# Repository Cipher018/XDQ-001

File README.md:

# XDQ-001

## Introduction

## What is XDQ-001?

The **XDQ-001**, or **Experimental Drone Quadcopter Model 001**, is a flight platform with an original design. Its experimental objective is to achieve a FPV quadcopter capable of both acrobatic flight and cinematic filming. Furthermore, the XDQ-001 platform serves as a cutting-edge testbed for implementing highly optimized low-level control and autonomous navigation algorithms.

## Whats New?

The **XDQ-001** represents a massive generational leap over its predecessor (XDF-001), integrating the following hardware and firmware innovations (Version V001):

1. **Hybrid Cooperative Interrupt-Based Architecture (No RTOS):**
   - **1000Hz Critical Loop:** Hardware Timer ISR dedicated exclusively to attitude (AHRS), PID calculations, and motor control.
   - **50Hz Kinematic Loop:** Background loop for Kalman filtering, waypoint navigation, and geometric estimation.
2. **Dual-Layer Navigation System:**
   - **Layer 1 (Attitude):** Optimized Mahony AHRS filter running at 1000Hz.
   - **Layer 2 (Kinematics):** Three-Dimensional Error State Kalman Filter (3D ESKF) at 50Hz, fusing accelerometer, GPS, and barometer (BMP280) measurements.
3. **CADI_A Adaptive Navigation System:**
   - Advanced algorithms for L1 navigation (adaptive waypoints) and Orbit (loiter).
   - **Stochastic Wind Estimator (Pitot-less):** Calculates and compensates for crosswind in real-time without requiring a pitot tube, based on geometric discrepancy during turns.
4. **Advanced Flight Control (FlightPID):** Isolated bandwidth PIDs (LPF_PT1 filters on P and D terms).
5. **Dynamic Safety Guards:**
   - *Dynamic Stall Guard:* Dynamic stall prevention based on bank angle.
   - *G-Limiter:* Pilot control limitation when the safe structural G-load (2.0G - 3.5G) is exceeded.
   - *Failsafe RTL:* Safe automatic Return-To-Launch on link loss.
6. **Dedicated Hardware:** MCU STM32F4 (with FPU), dedicated ICM-42688 IMU, MMC5983MA external magnetometer, and SX1280 long-range modem.
7. **Secure Communications & Telemetry:** Frequency Hopping Spread Spectrum (FHSS), logical dual-pipe, and strong cross-block encryption (XXTEA) with integrated CRC16.
8. **Uninterrupted Blackbox Logging:** Lock-free Ping-Pong buffers linked via DMA to the W25Q32JVSS Flash memory.

## Objectives

The primary objective is to develop an exceptional FPV quadcopter capable of both extreme acrobatic flight and smooth cinematic tracking.

The secondary objectives are:
- Provide an ultra-fast, predictable, non-RTOS software framework.
- Consolidate the capabilities of the CADI autonomous ecosystem (Waypoints, Orbits, auto RTL).
- Implement and refine stochastic estimation systems (ESKF and Wind Estimator).
- Establish an impenetrable telemetry system (robust encryption and FHSS).

## Architecture

As previously mentioned, the project is based on the STM32F4 architecture utilizing a hybrid cooperative interrupt-based system. You can consult the documentation section for details regarding the PCB, algorithms, or flowcharts.

## Hardware

The XDQ-001 uses a custom Flight Control Board (FCB) built around the **STM32F4** microcontroller. Key sensors and components:

- **IMU (Gyro/Accel):** ICM‑42688‑P
- **Magnetometer:** MMC5983MA
- **Barometer:** BMP280
- **Radio Link:** SX‑1280 (FHSS Support)
- **Storage:** W25Q32JVSS Flash Memory
- **Camera:** Caddx Baby Ratel 2 (optional)

A full Bill of Materials (BOM) is still being defined.

## Software

- Development is currently performed using the **Arduino IDE** (with the STM32 core) but migration to a more advanced toolchain is planned.
- No ground control station (GCS) software exists yet; a future GCS will communicate via the SX‑1280 radio.

## Compilation & Installation

The firmware follows the standard Arduino IDE project layout:

1. Open the `Firmware/` folder and load `XDQ-001F_V001.ino`.
2. Select the appropriate **STM32F4** board definition.
3. Ensure FPU support is enabled if required.
4. Verify / compile the sketch (`Ctrl+R`) and upload using a compatible programmer (e.g., ST-Link V2) or USB DFU bootloader.

## Usage

1. Power the FCB and connect the radio module.
2. Power the drone and perform a basic motor test (ensure propellers are removed).
3. When the GCS becomes available, pair it with the SX‑1280 radio and start telemetry.

## Configuration

At present the firmware has no runtime‑configurable parameters. Future releases will expose PID and filter tuning via the GCS.

## Contributing

Contributions are welcome under an **MIT license**. Please:

- Fork the repository and create a feature branch.
- Follow the existing code style (Arduino‑C++ with descriptive comments).
- Ensure any additions maintain the non-blocking philosophy of the 1000Hz critical loop.
- Open a Pull Request with a clear description of changes.

## License

This project is licensed under the **MIT License**. See the `LICENSE` file for details.

## Documentation

It is highly recommended to review the comprehensive documentation to understand the mathematical and algorithmic details:

- 📄 **[Firmware Reference Manual (Markdown)](Documentation/firmware_reference.md)**
- 📕 **[Firmware Reference Manual (PDF)](Documentation/firmware_reference.pdf)**
- 📐 [Architecture Diagram](Documentation/architecture.md) (Pending migration)
- 🔌 [Pinout & Hardware](Documentation/pinout.md) (Pending migration)
- 📡 [Protocols](Documentation/protocol.md) (Pending migration)

## Project Structure

The repository is organized as follows:

- **Firmware/** – Arduino sketch source files (`*.ino`, drivers, control algorithms, telemetry).
- **Documentation/** – Design documents, architecture diagrams, pin‑out tables, protocol specifications, and other reference material.
- **CAD/** – 3D models and mechanical drawings for printable parts.
- **PCB/** – PCB design files, gerbers, and component placement.
- **References/** – Datasheets, application notes, and external resources used during development.
- **README.md** – This high‑level overview.
- **LICENSE** – MIT license file.

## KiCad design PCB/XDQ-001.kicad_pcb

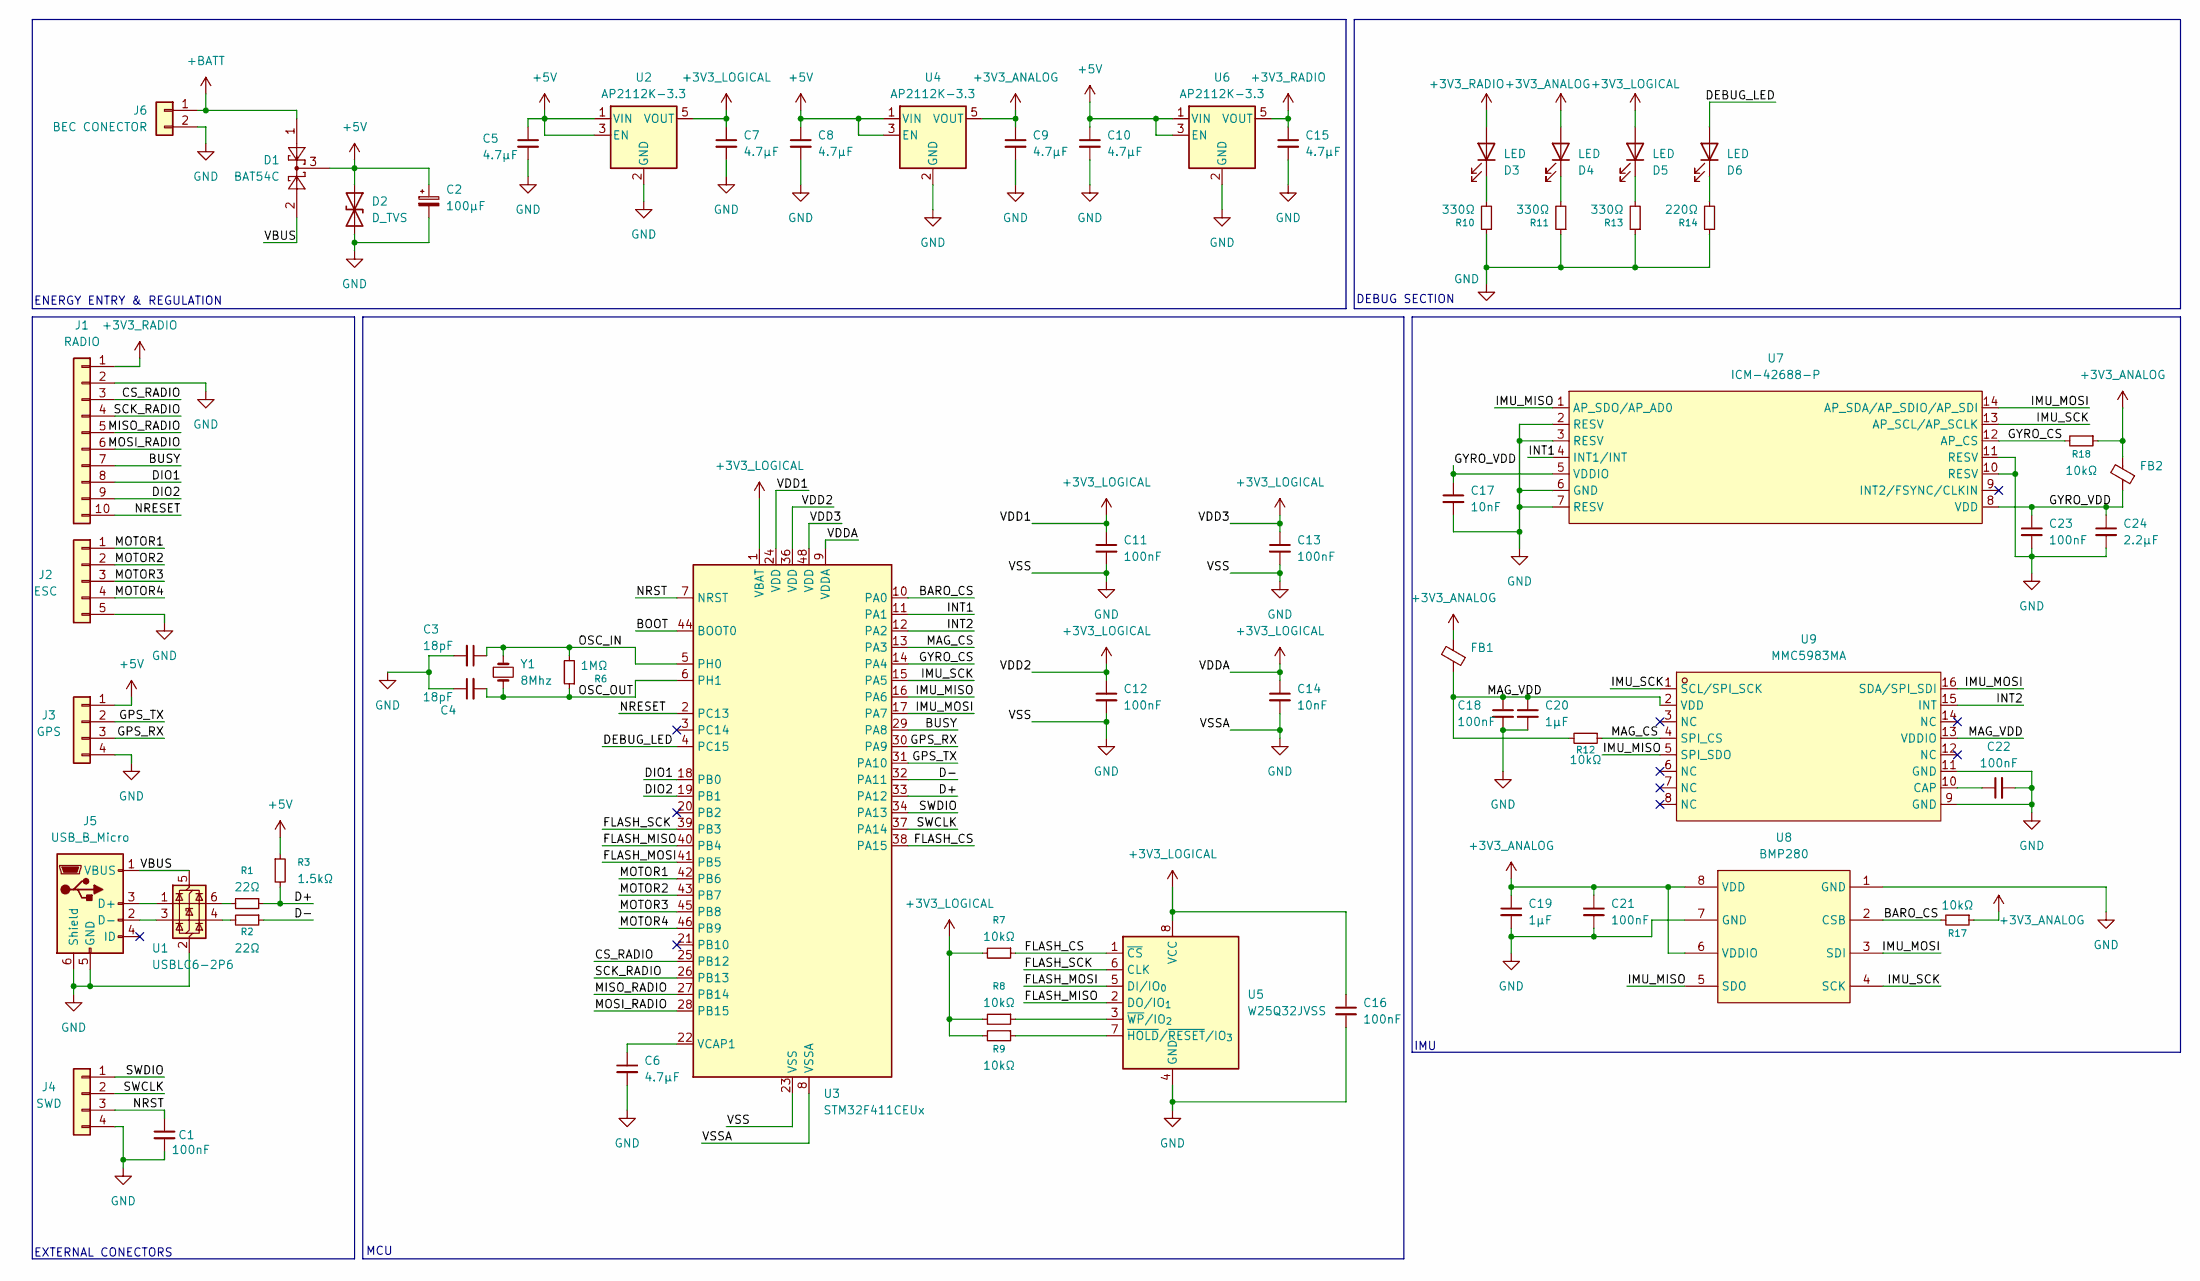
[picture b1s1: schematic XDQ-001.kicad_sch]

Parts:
C1, C11, C12, C13, C16, C18, C21, C22, C23: 100nF; C_0402_1005Metric_Pad0.74x0.62mm_HandSolder
C2: 100µF; CP_Elec_5x5.3
C3, C4: 18pF; C_0402_1005Metric_Pad0.74x0.62mm_HandSolder
C5, C6, C7, C8, C9, C10, C15: 4.7µF; C_0603_1608Metric_Pad1.08x0.95mm_HandSolder
C14, C17: 10nF; C_0402_1005Metric_Pad0.74x0.62mm_HandSolder
C19, C20: 1µF; C_0603_1608Metric_Pad1.08x0.95mm_HandSolder
C24: 2.2µF; C_0402_1005Metric_Pad0.74x0.62mm_HandSolder
D1: BAT54C; SOT-23
D2: D_TVS; D_SMB
D3, D4, D5, D6: LED; LED_0603_1608Metric_Pad1.05x0.95mm_HandSolder
FB1, FB2: FerriteBead_Small; L_0402_1005Metric
J1: RADIO; SolderWirePad_1x10_SMD_1.5x3mm
J2: ESC; SolderWirePad_1x05_SMD_1.5x3mm
J3: GPS; JST_PH_B4B-PH-K_1x04_P2.00mm_Vertical
J4: SWD; JST_PH_B4B-PH-K_1x04_P2.00mm_Vertical
J5: USB_B_Micro; USB_Micro-B_GCT_USB3076-30-A
J6: BEC CONECTOR; JST_PH_B2B-PH-K_1x02_P2.00mm_Vertical
R1, R2: 22Ω; R_0402_1005Metric_Pad0.72x0.64mm_HandSolder
R3: 1.5kΩ; R_0402_1005Metric_Pad0.72x0.64mm_HandSolder
R6: 1MΩ; R_0402_1005Metric_Pad0.72x0.64mm_HandSolder
R7, R8, R9, R12, R17, R18: 10kΩ; R_0402_1005Metric_Pad0.72x0.64mm_HandSolder
R10, R11, R13: 330Ω; R_0402_1005Metric_Pad0.72x0.64mm_HandSolder
R14: 220Ω; R_0402_1005Metric_Pad0.72x0.64mm_HandSolder
U1: USBLC6-2P6; SOT-666
U2, U4, U6: AP2112K-3.3; SOT-23-5
U3: STM32F411CEUx; QFN-48-1EP_7x7mm_P0.5mm_EP5.6x5.6mm
U5: W25Q32JVSS; SOIC-8_5.3x5.3mm_P1.27mm
U7: ICM-42688-P; LGA-14_L3.0-W2.5-P0.50-TL; MPN ICM-42688-P; LCSC Part C1850418
U8: BMP280; LGA-8_L2.5-W2.0-P0.65_AMP6127; MPN BMP280; LCSC Part C83291
U9: MMC5983MA; LGA-16_L3.0-W3.0-P0.50-BL_SQ; MPN MMC5983MA; LCSC Part C404329
Y1: 8Mhz; Crystal_SMD_2012-2Pin_2.0x1.2mm_HandSoldering

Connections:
+3V3_ANALOG: C9.1, C19.1, C21.1, D4.2 (A), FB1.2, FB2.2, R17.1, R18.1, U4.5 (VOUT), U8.6 (VDDIO), U8.8 (VDD)
+3V3_LOGICAL: C7.1, C11.1, C12.1, C13.1, C14.1, C16.1, D5.2 (A), R7.2, R8.2, R9.2, U2.5 (VOUT), U3.1 (VBAT), U3.9 (VDDA), U3.24 (VDD), U3.36 (VDD), U3.48 (VDD), U5.8 (VCC)
+3V3_RADIO: C15.1, D3.2 (A), J1.1, U6.5 (VOUT)
+5V: C2.1, C5.1, C8.1, C10.1, D1.3, D2.1 (A1), J3.1, R3.1, U2.1 (VIN), U2.3 (EN), U4.1 (VIN), U4.3 (EN), U6.1 (VIN), U6.3 (EN)
+BATT: D1.1, J6.1
/BARO_CS: R17.2, U3.10 (PA0), U8.2 (CSB)
/BOOT: U3.44 (BOOT0)
/BUSY: J1.7, U3.29 (PA8)
/CS_RADIO: J1.3, U3.25 (PB12)
/D+: R1.1, R3.2, U3.33 (PA12)
/D-: R2.1, U3.32 (PA11)
/DEBUG_LED: D6.2 (A), U3.4 (PC15)
/DIO1: J1.8, U3.18 (PB0)
/DIO2: J1.9, U3.19 (PB1)
/FLASH_CS: R7.1, U3.38 (PA15), U5.1 (~CS)
/FLASH_MISO: U3.40 (PB4), U5.2 (DO/IO_{1})
/FLASH_MOSI: U3.41 (PB5), U5.5 (DI/IO_{0})
/FLASH_SCK: U3.39 (PB3), U5.6 (CLK)
/GPS_RX: J3.3, U3.30 (PA9)
/GPS_TX: J3.2, U3.31 (PA10)
/GYRO_CS: R18.2, U3.14 (PA4), U7.12 (AP_CS)
/GYRO_VDD: C17.1, C23.1, C24.1, FB2.1, U7.5 (VDDIO), U7.8 (VDD)
/IMU_MISO: U3.16 (PA6), U7.1 (AP_SDO/AP_AD0), U8.5 (SDO), U9.5 (SPI_SDO)
/IMU_MOSI: U3.17 (PA7), U7.14 (AP_SDA/AP_SDIO/AP_SDI), U8.3 (SDI), U9.16 (SDA/SPI_SDI)
/IMU_SCK: U3.15 (PA5), U7.13 (AP_SCL/AP_SCLK), U8.4 (SCK), U9.1 (SCL/SPI_SCK)
/INT1: U3.11 (PA1), U7.4 (INT1/INT)
/INT2: U3.12 (PA2), U9.15 (INT)
/MAG_CS: R12.1, U3.13 (PA3), U9.4 (SPI_CS)
/MAG_VDD: C18.1, C20.1, FB1.1, R12.2, U9.2 (VDD), U9.13 (VDDIO)
/MISO_RADIO: J1.5, U3.27 (PB14)
/MOSI_RADIO: J1.6, U3.28 (PB15)
/MOTOR1: J2.1, U3.42 (PB6)
/MOTOR2: J2.2, U3.43 (PB7)
/MOTOR3: J2.3, U3.45 (PB8)
/MOTOR4: J2.4, U3.46 (PB9)
/NRESET: J1.10, U3.2 (PC13)
/NRST: C1.1, J4.3, U3.7 (NRST)
/OSC_IN: C3.1, R6.2, U3.5 (PH0), Y1.1
/OSC_OUT: C4.2, R6.1, U3.6 (PH1), Y1.2
/SCK_RADIO: J1.4, U3.26 (PB13)
/SWCLK: J4.2, U3.37 (PA14)
/SWDIO: J4.1, U3.34 (PA13)
/VBUS: D1.2, J5.1 (VBUS), U1.5 (VBUS)
GND: C1.2, C2.2, C3.2, C4.1, C5.2, C6.2, C7.2, C8.2, C9.2, C10.2, C11.2, C12.2, C13.2, C14.2, C15.2, C16.2, C17.2, C18.2, C19.2, C20.2, C21.2, C22.2, C23.2, C24.2, D2.2 (A2), J1.2, J2.5, J3.4, J4.4, J5.5 (GND), J5.6 (Shield), J6.2, R10.1, R11.1, R13.1, R14.1, U1.2 (GND), U2.2 (GND), U3.8 (VSSA), U3.23 (VSS), U3.35 (VSS), U3.47 (VSS), U3.49 (VSS), U4.2 (GND), U5.4 (GND), U6.2 (GND), U7.2 (RESV), U7.3 (RESV), U7.6 (GND), U7.7 (RESV), U7.10 (RESV), U7.11 (RESV), U8.1 (GND), U8.7 (GND), U9.9 (GND), U9.11 (GND)
unnamed: D3.1 (K), R10.2
unnamed: D4.1 (K), R11.2
unnamed: D5.1 (K), R13.2
unnamed: D6.1 (K), R14.2
unnamed: J5.3 (D+), U1.1 (I/O1)
unnamed: J5.2 (D-), U1.3 (I/O2)
unnamed: R1.2, U1.6 (I/O1)
unnamed: R2.2, U1.4 (I/O2)
unnamed: C6.1, U3.22 (VCAP1)
unnamed: R9.1, U5.7 (~HOLD/~RESET/IO_{3})
unnamed: R8.1, U5.3 (~WP/IO_{2})
unnamed: C22.1, U9.10 (CAP)

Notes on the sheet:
EXTERNAL CONECTORS
DEBUG SECTION
IMU
MCU
ENERGY ENTRY & REGULATION

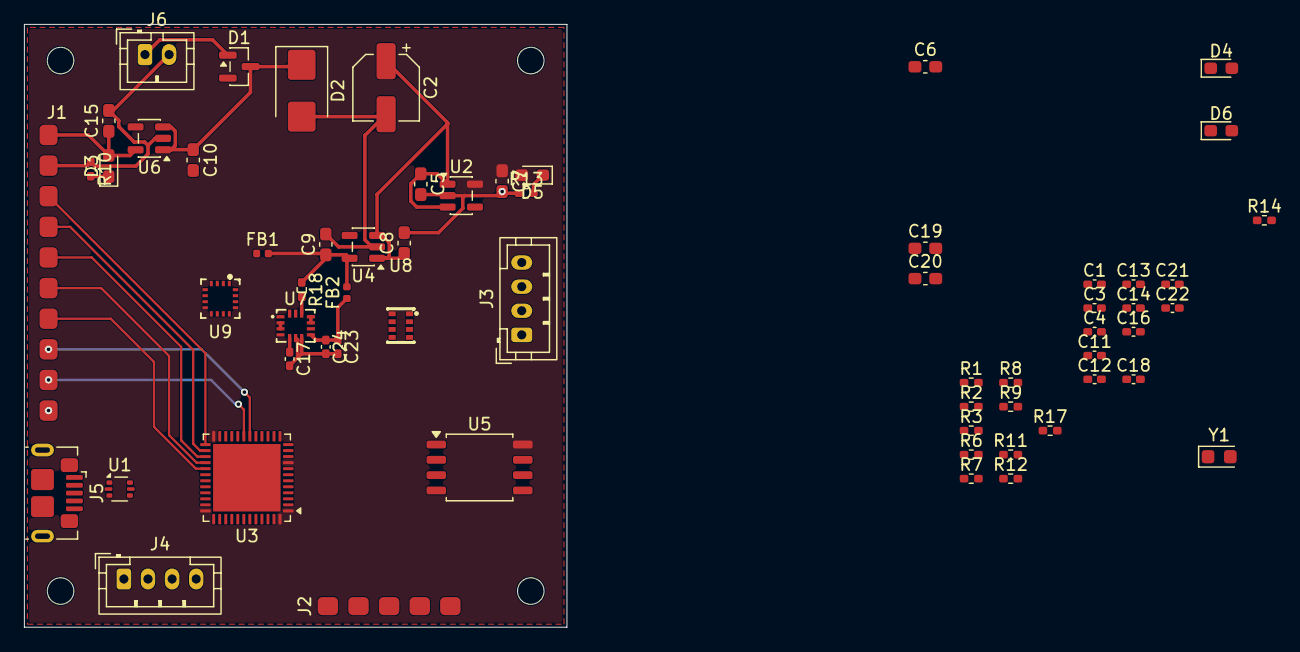
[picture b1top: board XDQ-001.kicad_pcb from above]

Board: 4 copper layers, 45.0 x 50.0 mm, 62 parts (0 on the bottom side), 55 nets.

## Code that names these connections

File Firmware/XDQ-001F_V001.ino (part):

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// ── DEFINICIÓN DE PINES (Asignación física de la placa XDQ-001) ──

// Bus SPI 3: Memoria Flash W25Q32JVSS
#define PIN_FLASH_SCK PB3
#define PIN_FLASH_MISO PB4
#define PIN_FLASH_MOSI PB5
#define PIN_FLASH_CS PA15

// Bus SPI 1: Sensores IMU, Magnetómetro, Barómetro
#define PIN_SPI1_SCK PA5
#define PIN_SPI1_MISO PA6
#define PIN_SPI1_MOSI PA7
#define PIN_ICM_CS PA4  // CS Giroscopio / Acelerómetro (ICM-42688)
#define PIN_MAG_CS PA3  // CS Magnetómetro (MMC5983MA)
#define PIN_BARO_CS PA0 // CS Barómetro (BMP280)
#define PIN_ICM_INT PA1 // Interrupción IMU
#define PIN_MAG_INT PA2 // Interrupción Magnetómetro

// Motores (ESC 4-in-1 - Salidas PWM)
#define PIN_MOTOR_1 PB6
#define PIN_MOTOR_2 PB7
#define PIN_MOTOR_3 PB8
#define PIN_MOTOR_4 PB9

// Bus SPI 2: Radio SX1280
#define PIN_RADIO_CS PB12
#define PIN_RADIO_SCK PB13
#define PIN_RADIO_MISO PB14
#define PIN_RADIO_MOSI PB15
#define PIN_RADIO_BUSY PA8
#define PIN_RADIO_RST PC13
#define PIN_RADIO_DIO1 PB0
#define PIN_RADIO_DIO2 PB1

// GPS NEO-6M (USART1)
#define PIN_GPS_RX PA10 // Conecta a TX del GPS (STM32 RX)
#define PIN_GPS_TX PA9  // Conecta a RX del GPS (STM32 TX)

// Debug LED
#define PIN_DEBUG_LED PC15

// ── INSTANCIAS DE BUSES SPI Y UART ──
SPIClass SPI_Sensors(PIN_SPI1_MOSI, PIN_SPI1_MISO, PIN_SPI1_SCK);
SPIClass SPI_Radio(PIN_RADIO_MOSI, PIN_RADIO_MISO, PIN_RADIO_SCK);
SPIClass SPI_Flash(PIN_FLASH_MOSI, PIN_FLASH_MISO, PIN_FLASH_SCK);

#define GPS_Serial Serial1

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
void read_magnetometer() {
  SPI_Sensors.beginTransaction(SPISettings(10000000, MSBFIRST, SPI_MODE0));
  digitalWrite(PIN_MAG_CS, LOW);
  SPI_Sensors.transfer(0x06);
  int16_t mx = (SPI_Sensors.transfer(0x00) << 8) | SPI_Sensors.transfer(0x00);
  int16_t my = (SPI_Sensors.transfer(0x00) << 8) | SPI_Sensors.transfer(0x00);
  int16_t mz = (SPI_Sensors.transfer(0x00) << 8) | SPI_Sensors.transfer(0x00);
  digitalWrite(PIN_MAG_CS, HIGH);
  SPI_Sensors.endTransaction();
}

void read_barometer() {
  SPI_Sensors.beginTransaction(SPISettings(10000000, MSBFIRST, SPI_MODE0));
  digitalWrite(PIN_BARO_CS, LOW);
  SPI_Sensors.transfer(0xF7 | 0x80);
  int32_t raw_p = ((uint32_t)SPI_Sensors.transfer(0x00) << 12) |
                  ((uint32_t)SPI_Sensors.transfer(0x00) << 4) |
                  (SPI_Sensors.transfer(0x00) >> 4);
  digitalWrite(PIN_BARO_CS, HIGH);
  SPI_Sensors.endTransaction();

  altitudeM = 44330.0f * (1.0f - powf((float)raw_p / 101325.0f, 0.1903f));
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
bool w25q32_is_busy() {
  SPI_Flash.beginTransaction(SPISettings(40000000, MSBFIRST, SPI_MODE0));
  digitalWrite(PIN_FLASH_CS, LOW);
  SPI_Flash.transfer(0x05);
  uint8_t status = SPI_Flash.transfer(0x00);
  digitalWrite(PIN_FLASH_CS, HIGH);
  SPI_Flash.endTransaction();
  return (status & 0x01);
}

void w25q32_write_page(uint32_t address, const uint8_t *data) {
  SPI_Flash.beginTransaction(SPISettings(40000000, MSBFIRST, SPI_MODE0));
  digitalWrite(PIN_FLASH_CS, LOW);
  SPI_Flash.transfer(0x06);
  digitalWrite(PIN_FLASH_CS, HIGH);
  SPI_Flash.endTransaction();

  SPI_Flash.beginTransaction(SPISettings(40000000, MSBFIRST, SPI_MODE0));
  digitalWrite(PIN_FLASH_CS, LOW);
  SPI_Flash.transfer(0x02);
  SPI_Flash.transfer((address >> 16) & 0xFF);
  SPI_Flash.transfer((address >> 8) & 0xFF);
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  for (uint16_t i = 0; i < FLASH_PAGE_SIZE; i++) {
    SPI_Flash.transfer(data[i]);
  }
  digitalWrite(PIN_FLASH_CS, HIGH);
  SPI_Flash.endTransaction();
}

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// ── SETUP & INITIALIZATION ──

void setup() {
  pinMode(PIN_DEBUG_LED, OUTPUT);
  digitalWrite(PIN_DEBUG_LED, HIGH);

  Serial.begin(115200);
  GPS_Serial.begin(9600);

  pinMode(PIN_ICM_CS, OUTPUT);
  pinMode(PIN_MAG_CS, OUTPUT);
  pinMode(PIN_BARO_CS, OUTPUT);
  pinMode(PIN_RADIO_CS, OUTPUT);
  pinMode(PIN_FLASH_CS, OUTPUT);
  digitalWrite(PIN_ICM_CS, HIGH);
  digitalWrite(PIN_MAG_CS, HIGH);
  digitalWrite(PIN_BARO_CS, HIGH);
  digitalWrite(PIN_RADIO_CS, HIGH);
  digitalWrite(PIN_FLASH_CS, HIGH);

  SPI_Sensors.begin();
  SPI_Radio.begin();
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  Timer_1kHz->resume();
#endif

  digitalWrite(PIN_DEBUG_LED, LOW);
}

// ── LOOP PRINCIPAL COOPERATIVO (FONDO - 50Hz) ──
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    float dt = (now - last_loop_50hz) / 1000.0f;
    last_loop_50hz = now;

    digitalWrite(PIN_DEBUG_LED, !digitalRead(PIN_DEBUG_LED));

    // 1. Navegación Lazo Externo (Lecturas y ESKF Inercial a 50Hz)
    read_magnetometer();
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
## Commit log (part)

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2026-06-13 Initial post
2026-06-13 Deleted temp files
2026-06-13 Creating root files
2026-06-23 feat: initialize project directory with KiCad design files, firmware, and reference documentation
2026-06-23 Started to write the README
2026-06-28 feat: Created gerbers and CAD files
2026-06-29 feat: initialize new KiCad project files and update README
